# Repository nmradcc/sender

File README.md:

# sender
NMRA Conformance Test Software

This branch contains a refactor of the B 5.11.5 (V3-archive branch) reworked and retooled to support operation on modern PC (64bit Windows) with attached STM32 Nucleo controller for timing and IO.

The build tools are upgraded to build under Visual Studio Code with CMake.

The VSC C/C++ Extension Pack and CMake Tools extensions are required.

You can use the Visual Studio Build Tools 2022 Release - x86 as the build kit but others may work also.

There are two projects:
1. The host PC software
2. The STM32 controller (MCU) software

The send configuration files (*.INI) have been reworked to accept *.cfg files of the same format.

It will also accept legacy .INI files but is discuraged as using .INI files for parameter passing is a no-no in todays world.

Much of the documentation may still show .INI

Most of old Visual Source Safe (scc stuff) has been remove. See the V3-archive branch for previous history.

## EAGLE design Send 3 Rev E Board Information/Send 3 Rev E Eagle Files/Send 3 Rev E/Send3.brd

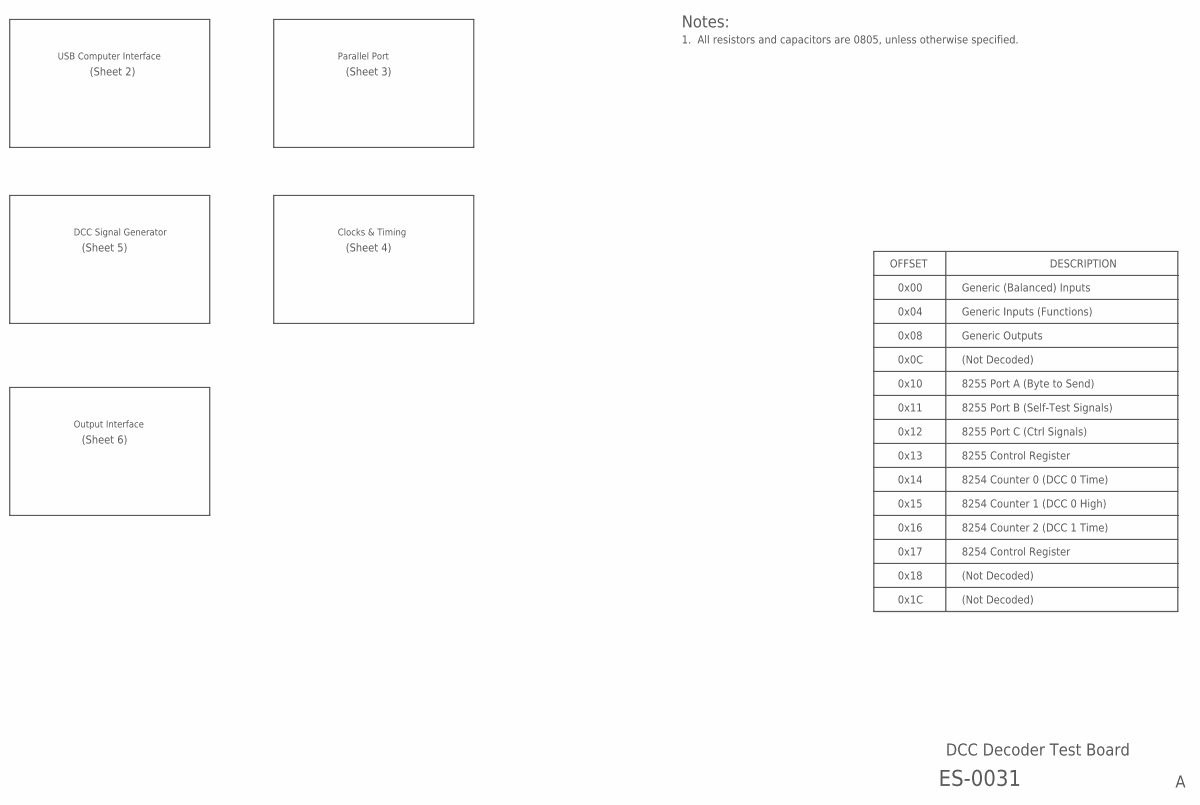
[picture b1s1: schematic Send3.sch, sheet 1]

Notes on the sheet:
USB Computer Interface
Notes:
1. All resistors and capacitors are 0805, unless otherwise specified.
Parallel Port
(Sheet 2)
(Sheet 3)
Clocks & Timing
(Sheet 4)
DCC Signal Generator
(Sheet 5)
Output Interface
(Sheet 6)
OFFSET
DESCRIPTION
0x00
0x04
0x08
0x10
0x11
0x12
0x13
0x14
0x15
0x16
0x17
Generic (Balanced) Inputs
Generic Inputs (Functions)
Generic Outputs
8255 Port A (Byte to Send)
8255 Port B (Self-Test Signals)
8255 Port C (Ctrl Signals)
8255 Control Register
8254 Counter 0 (DCC 0 Time)
8254 Counter 1 (DCC 0 High)
8254 Counter 2 (DCC 1 Time)
8254 Control Register
0x0C
0x18
0x1C
(Not Decoded)

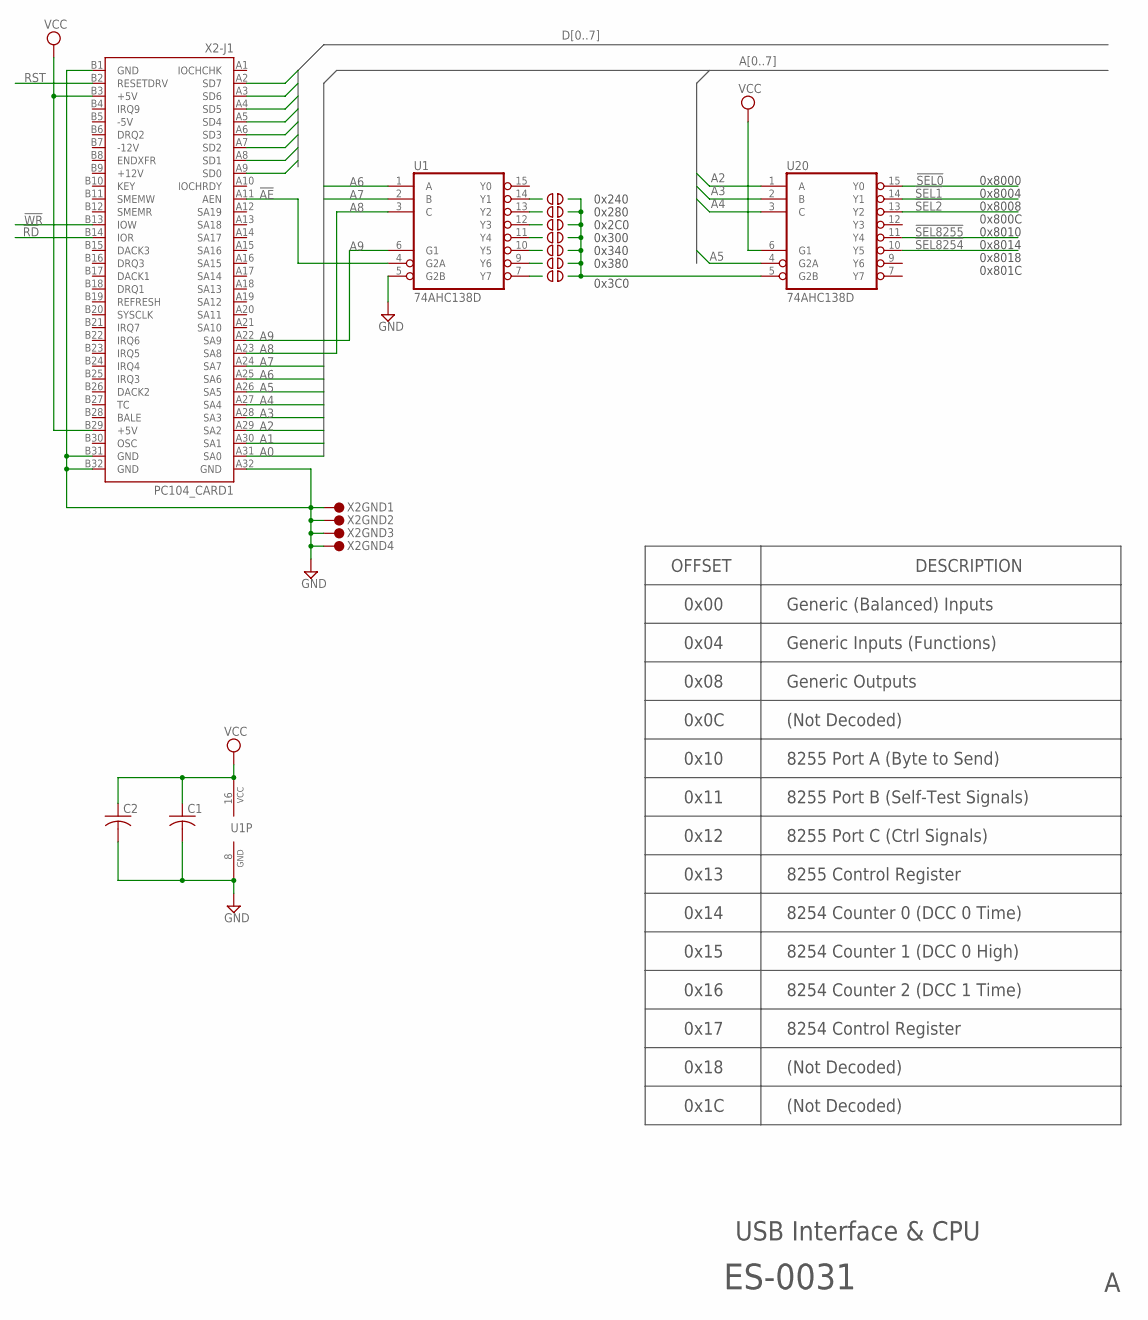
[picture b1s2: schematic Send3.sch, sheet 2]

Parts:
C1, C2: C-USC0805K; C0805K; MFG_PN ECJ-2VB1E104K
JMPR2, JMPR3, JMPR4, JMPR5, JMPR6, JMPR7, JMPR8: JUMPER; SOLDER_BRIDGE
U1, U20: 74AHC138D; SO16; MFG_PN SN74AHC138D
X2: PC104_CARD1; PC104-STANDARD

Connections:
!AE: U1.4 (G2A), X2.A11 (AEN)
!RD: X2.B14 (IOR); also elsewhere on the board
!SEL0: U20.15 (Y0); also elsewhere on the board
!SEL1: U20.14 (Y1); also elsewhere on the board
!SEL2: U20.13 (Y2); also elsewhere on the board
!SEL8254: U20.10 (Y5); also elsewhere on the board
!SEL8255: U20.11 (Y4); also elsewhere on the board
!WR: X2.B13 (IOW); also elsewhere on the board
A0: X2.A31 (SA0); also elsewhere on the board
A1: X2.A30 (SA1); also elsewhere on the board
A2: U20.1 (A), X2.A29 (SA2)
A3: U20.2 (B), X2.A28 (SA3)
A4: U20.3 (C), X2.A27 (SA4)
A5: U20.4 (G2A), X2.A26 (SA5)
A6: U1.1 (A), X2.A25 (SA6)
A7: U1.2 (B), X2.A24 (SA7)
A8: U1.3 (C), X2.A23 (SA8)
A9: U1.6 (G1), X2.A22 (SA9)
D0: X2.A9 (SD0); also elsewhere on the board
D1: X2.A8 (SD1); also elsewhere on the board
D2: X2.A7 (SD2); also elsewhere on the board
D3: X2.A6 (SD3); also elsewhere on the board
D4: X2.A5 (SD4); also elsewhere on the board
D5: X2.A4 (SD5); also elsewhere on the board
D6: X2.A3 (SD6); also elsewhere on the board
D7: X2.A2 (SD7); also elsewhere on the board
GND: C1.2, C2.2, U1.5 (G2B), U1.8 (GND), U20.8 (GND), X2.A32 (GND), X2.B1 (GND), X2.B31 (GND), X2.B32 (GND), X2.GND@1 (1), X2.GND@2 (1), X2.GND@3 (1), X2.GND@4 (1); also elsewhere on the board
unnamed: JMPR2.P$1, U1.14 (Y1)
unnamed: JMPR3.P$1, U1.13 (Y2)
unnamed: JMPR4.P$1, U1.12 (Y3)
unnamed: JMPR5.P$1, U1.11 (Y4)
unnamed: JMPR6.P$1, U1.10 (Y5)
unnamed: JMPR7.P$1, U1.9 (Y6)
unnamed: JMPR8.P$1, U1.7 (Y7)
unnamed: JMPR2.P$2, JMPR3.P$2, JMPR4.P$2, JMPR5.P$2, JMPR6.P$2, JMPR7.P$2, JMPR8.P$2, U20.5 (G2B)
RST: X2.B2 (RESETDRV); also elsewhere on the board
VCC: C1.1, C2.1, U1.16 (VCC), U20.6 (G1), U20.16 (VCC), X2.B3 (+5V), X2.B29 (+5V); also elsewhere on the board

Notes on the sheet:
USB Interface & CPU
OFFSET
DESCRIPTION
0x00
0x04
0x08
0x10
0x11
0x12
0x13
0x14
0x15
0x16
0x17
Generic (Balanced) Inputs
Generic Inputs (Functions)
Generic Outputs
8255 Port A (Byte to Send)
8255 Port B (Self-Test Signals)
8255 Port C (Ctrl Signals)
8255 Control Register
8254 Counter 0 (DCC 0 Time)
8254 Counter 1 (DCC 0 High)
8254 Counter 2 (DCC 1 Time)
8254 Control Register
0x0C
0x18
0x1C
(Not Decoded)
0x8000
0x8004
0x8008
0x800C
0x8010
0x8014
0x8018
0x801C
ES-0031
0x240
0x280

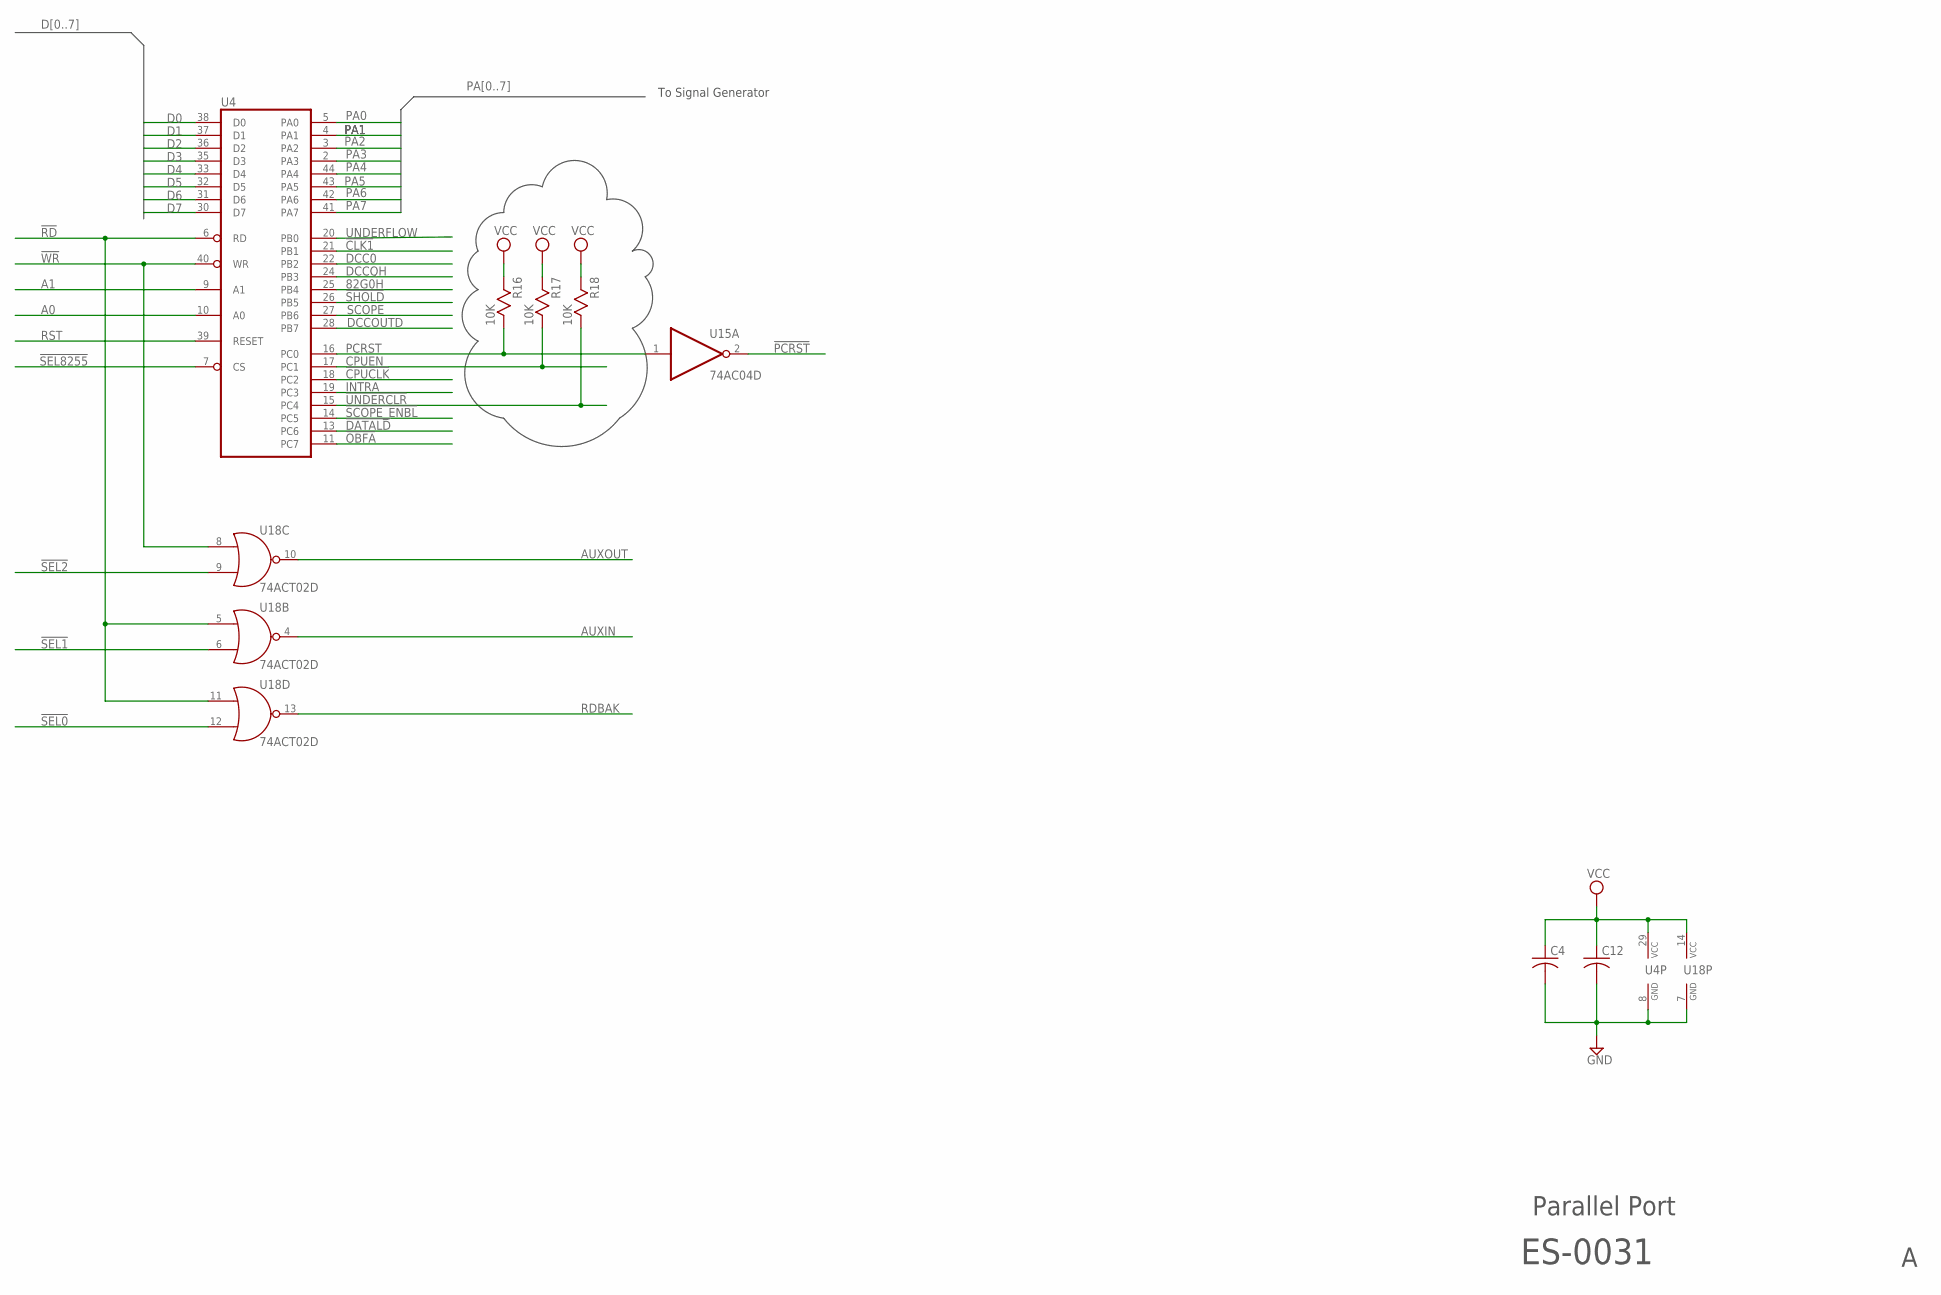
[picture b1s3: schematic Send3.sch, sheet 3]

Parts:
C4, C12: C-USC0805K; C0805K; MFG_PN ECJ-2VB1E104K
R16, R17, R18: 10K; R0805W; MFG_PN ERJ-P06J103V
U4: 8255A-S; PLCC44; MFG_PN CQ82C55AZ
U15: 74AC04D; SO14; MFG_PN SN74AHC04DR
U18: 74ACT02D; SO14; MFG_PN SN74AHC02DR

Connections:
82G0H: U4.25 (PB4); also elsewhere on the board
!CLK1: U4.21 (PB1); also elsewhere on the board
!CPUCLK: U4.18 (PC2); also elsewhere on the board
!DATALD: U4.13 (PC6); also elsewhere on the board
!OBFA: U4.11 (PC7); also elsewhere on the board
!PCRST: U15.2 (O); also elsewhere on the board
!RD: U4.6 (RD), U18.5 (I0), U18.11 (I0); also elsewhere on the board
!SCOPE_ENBL: U4.14 (PC5); also elsewhere on the board
!SEL0: U18.12 (I1); also elsewhere on the board
!SEL1: U18.6 (I1); also elsewhere on the board
!SEL2: U18.9 (I1); also elsewhere on the board
!SEL8255: U4.7 (CS); also elsewhere on the board
!SHOLD: U4.26 (PB5); also elsewhere on the board
!UNDERCLR: R18.2, U4.15 (PC4); also elsewhere on the board
!WR: U4.40 (WR), U18.8 (I0); also elsewhere on the board
A0: U4.10 (A0); also elsewhere on the board
A1: U4.9 (A1); also elsewhere on the board
AUXIN: U18.4 (O); also elsewhere on the board
AUXOUT: U18.10 (O); also elsewhere on the board
CPUEN: R17.2, U4.17 (PC1); also elsewhere on the board
D0: U4.38 (D0); also elsewhere on the board
D1: U4.37 (D1); also elsewhere on the board
D2: U4.36 (D2); also elsewhere on the board
D3: U4.35 (D3); also elsewhere on the board
D4: U4.33 (D4); also elsewhere on the board
D5: U4.32 (D5); also elsewhere on the board
D6: U4.31 (D6); also elsewhere on the board
D7: U4.30 (D7); also elsewhere on the board
DCC0: U4.22 (PB2); also elsewhere on the board
DCCOUTD: U4.28 (PB7); also elsewhere on the board
DCCQH: U4.24 (PB3); also elsewhere on the board
GND: C4.2, C12.2, U4.8 (GND), U18.7 (GND); also elsewhere on the board
INTRA: U4.19 (PC3)
PA0: U4.5 (PA0); also elsewhere on the board
PA1: U4.4 (PA1); also elsewhere on the board
PA2: U4.3 (PA2); also elsewhere on the board
PA3: U4.2 (PA3); also elsewhere on the board
PA4: U4.44 (PA4); also elsewhere on the board
PA5: U4.43 (PA5); also elsewhere on the board
PA6: U4.42 (PA6); also elsewhere on the board
PA7: U4.41 (PA7); also elsewhere on the board
PCRST: R16.2, U4.16 (PC0), U15.1 (I)
RDBAK: U18.13 (O); also elsewhere on the board
RST: U4.39 (RESET); also elsewhere on the board
SCOPE: U4.27 (PB6); also elsewhere on the board
UNDERFLOW: U4.20 (PB0); also elsewhere on the board
VCC: C4.1, C12.1, R16.1, R17.1, R18.1, U4.29 (VCC), U18.14 (VCC); also elsewhere on the board

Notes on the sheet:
Parallel Port
To Signal Generator
ES-0031

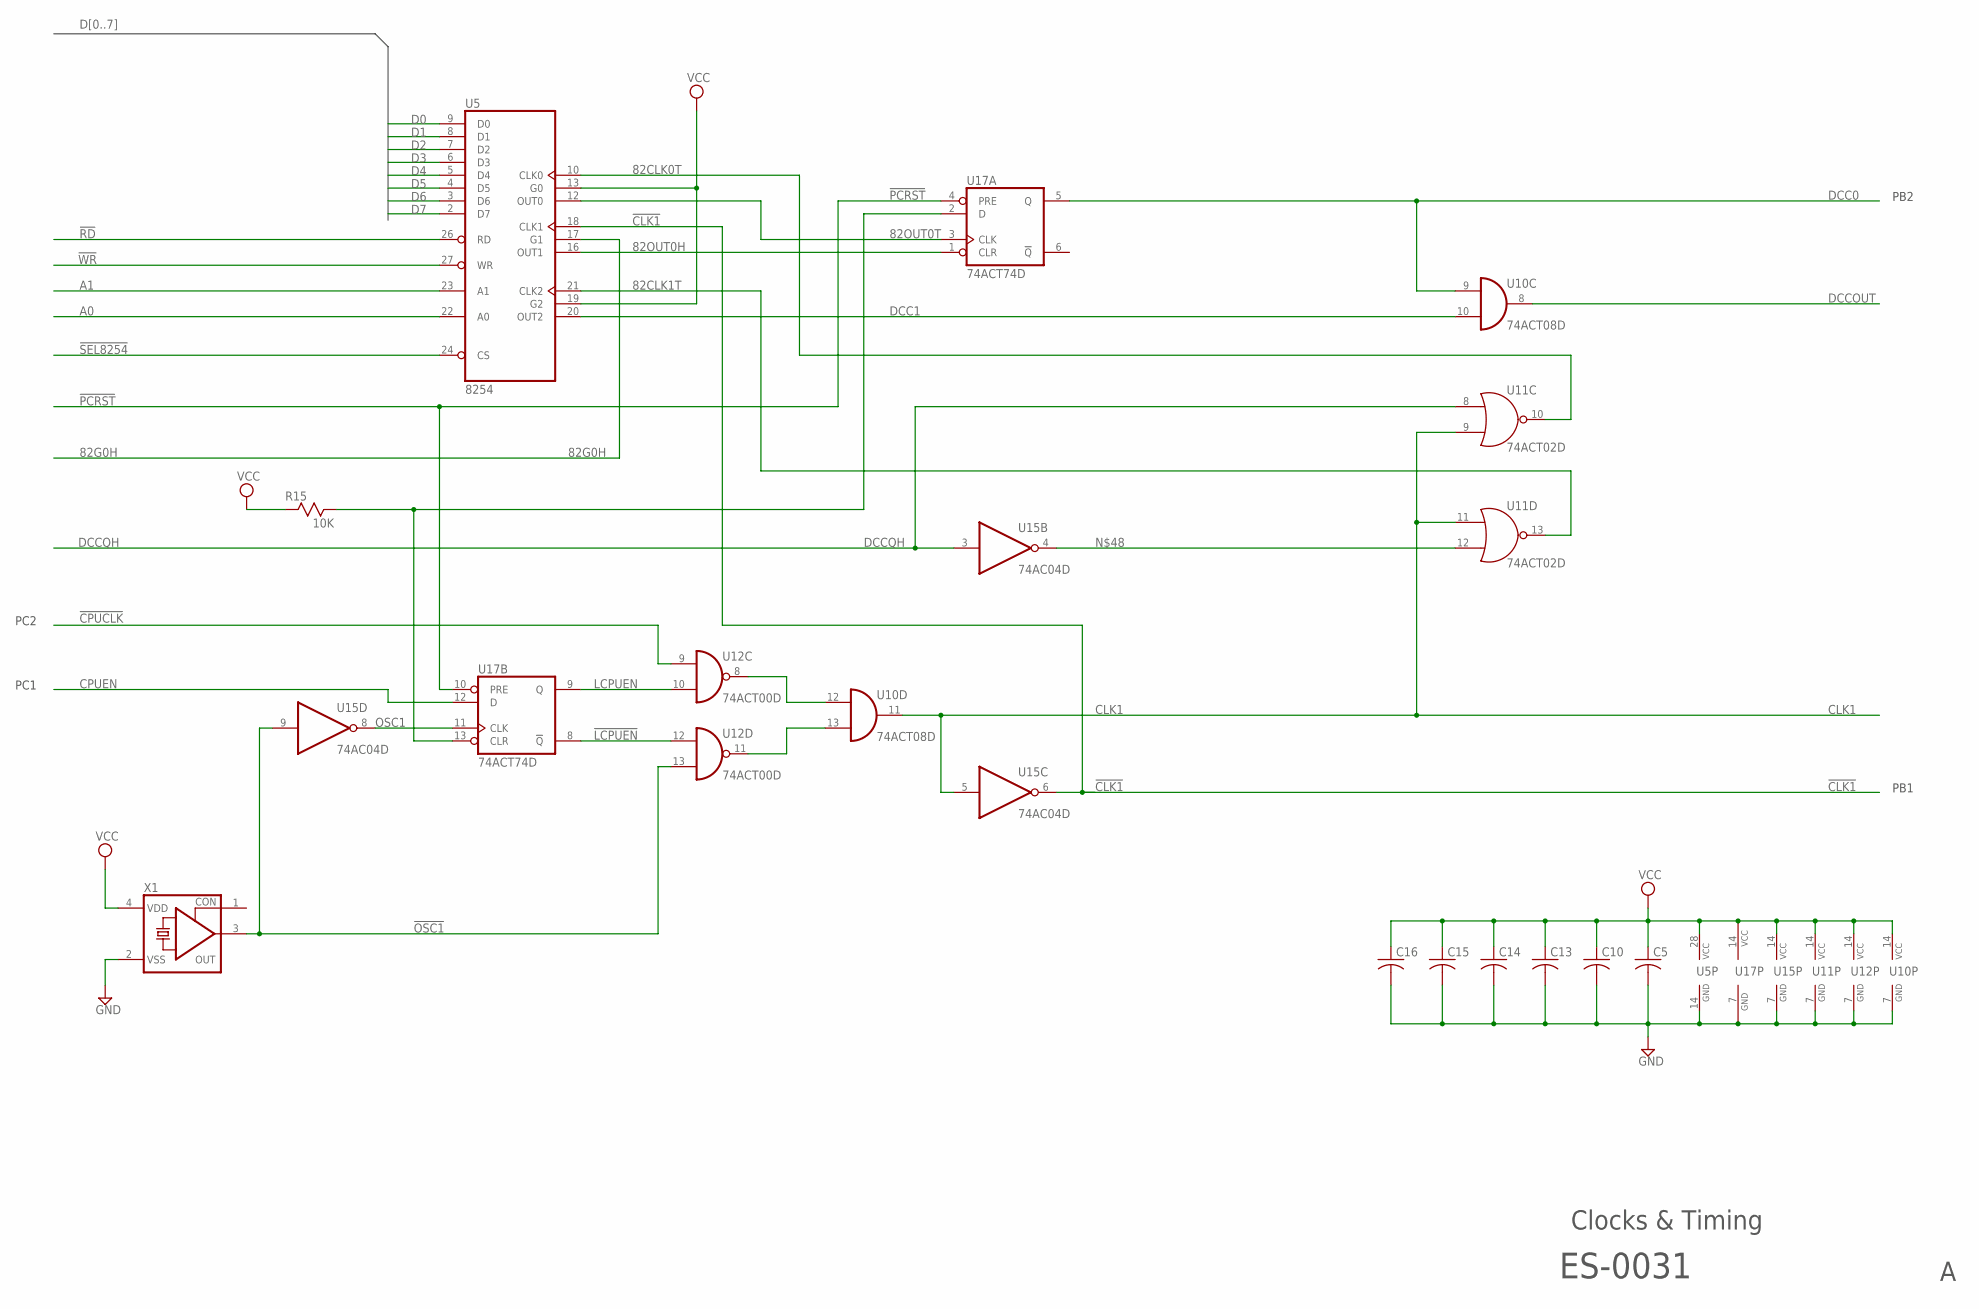
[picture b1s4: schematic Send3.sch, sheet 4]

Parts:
C5, C10, C13, C14, C15, C16: C-USC0805K; C0805K; MFG_PN ECJ-2VB1E104K
R15: 10K; R0805W; MFG_PN ERJ-P06J103V
U5: 8254; PLCC28S; MFG_PN CS82C54-10Z96
U10: 74ACT08D; SO14; MFG_PN SN74AHC08DR
U11: 74ACT02D; SO14; MFG_PN SN74AHC02DR
U12: 74ACT00D; SO14; MFG_PN SN74AHC00DR
U15: 74AC04D; SO14; MFG_PN SN74AHC04DR
U17: 74ACT74D; SO14; MFG_PN SN74AHC74DR
X1: CRYSTAL_RES-1100S; 1100S; MFG_PN ECS-8FM-1.00000

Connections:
82CLK0T: U5.10 (CLK0), U11.10 (O)
82CLK1T: U5.21 (CLK2), U11.13 (O)
82G0H: U5.17 (G1); also elsewhere on the board
82OUT0H: U5.16 (OUT1), U17.1 (CLR)
82OUT0T: U5.12 (OUT0), U17.3 (CLK)
!CLK1: U5.18 (CLK1), U15.6 (O); also elsewhere on the board
!CPUCLK: U12.9 (I0); also elsewhere on the board
!LCPUEN: U12.12 (I0), U17.8 (!Q)
!OSC1: U12.13 (I1), U15.9 (I), X1.3 (OUT)
!PCRST: U17.4 (PRE), U17.10 (PRE); also elsewhere on the board
!RD: U5.26 (RD); also elsewhere on the board
!SEL8254: U5.24 (CS); also elsewhere on the board
!WR: U5.27 (WR); also elsewhere on the board
A0: U5.22 (A0); also elsewhere on the board
A1: U5.23 (A1); also elsewhere on the board
CLK1: U10.11 (O), U11.9 (I1), U11.11 (I0), U15.5 (I); also elsewhere on the board
CPUEN: U17.12 (D); also elsewhere on the board
D0: U5.9 (D0); also elsewhere on the board
D1: U5.8 (D1); also elsewhere on the board
D2: U5.7 (D2); also elsewhere on the board
D3: U5.6 (D3); also elsewhere on the board
D4: U5.5 (D4); also elsewhere on the board
D5: U5.4 (D5); also elsewhere on the board
D6: U5.3 (D6); also elsewhere on the board
D7: U5.2 (D7); also elsewhere on the board
DCC0: U10.9 (I0), U17.5 (Q); also elsewhere on the board
DCC1: U5.20 (OUT2), U10.10 (I1)
DCCOUT: U10.8 (O); also elsewhere on the board
DCCQH: U11.8 (I0), U15.3 (I); also elsewhere on the board
GND: C5.2, C10.2, C13.2, C14.2, C15.2, C16.2, U5.14 (GND), U10.7 (GND), U11.7 (GND), U12.7 (GND), U15.7 (GND), U17.7 (GND), X1.2 (VSS); also elsewhere on the board
LCPUEN: U12.10 (I1), U17.9 (Q)
unnamed: U10.12 (I0), U12.8 (O)
unnamed: U10.13 (I1), U12.11 (O)
unnamed: U11.12 (I1), U15.4 (O)
OSC1: U15.8 (O), U17.11 (CLK)
PU403: R15.2, U17.2 (D), U17.13 (CLR)
VCC: C5.1, C10.1, C13.1, C14.1, C15.1, C16.1, R15.1, U5.13 (G0), U5.19 (G2), U5.28 (VCC), U10.14 (VCC), U11.14 (VCC), U12.14 (VCC), U15.14 (VCC), U17.14 (VCC), X1.4 (VDD); also elsewhere on the board

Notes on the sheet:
Clocks & Timing
PB2
PB1
PC1
PC2
ES-0031

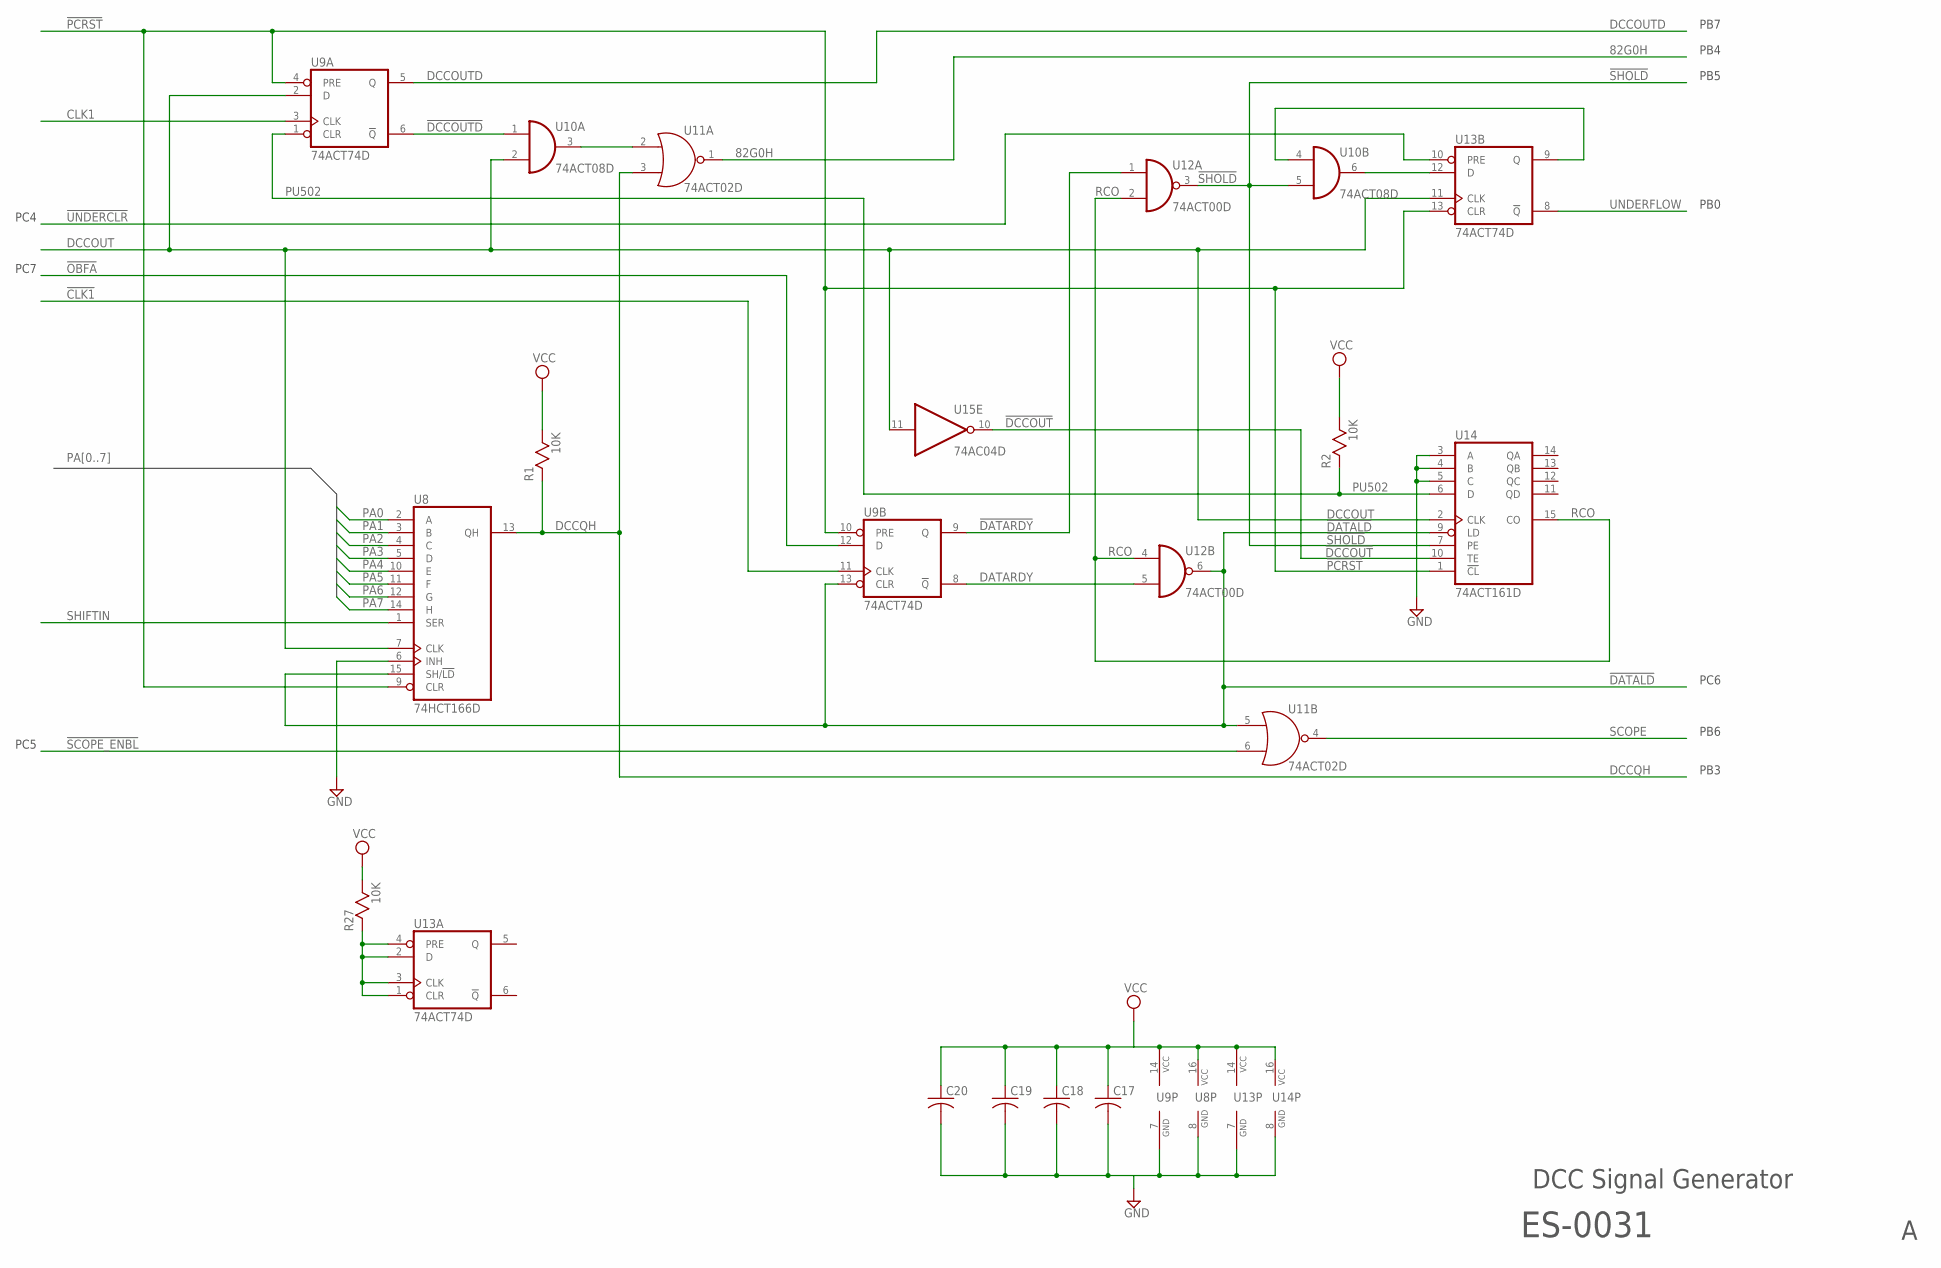
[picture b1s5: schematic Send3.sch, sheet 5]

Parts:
C17, C18, C19, C20: C-USC0805K; C0805K; MFG_PN ECJ-2VB1E104K
R1, R2, R27: 10K; R0805W; MFG_PN ERJ-P06J103V
U8: 74HCT166D; SO16; MFG_PN SN74HC166DR
U9, U13: 74ACT74D; SO14; MFG_PN SN74AHC74DR
U10: 74ACT08D; SO14; MFG_PN SN74AHC08DR
U11: 74ACT02D; SO14; MFG_PN SN74AHC02DR
U12: 74ACT00D; SO14; MFG_PN SN74AHC00DR
U14: 74ACT161D; SO16; MFG_PN CD74ACT161M
U15: 74AC04D; SO14; MFG_PN SN74AHC04DR

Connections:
82G0H: U11.1 (O); also elsewhere on the board
!CLK1: U9.11 (CLK); also elsewhere on the board
!DATALD: U8.15 (SH/!LD), U9.13 (CLR), U11.5 (I0), U12.6 (O), U14.9 (LD); also elsewhere on the board
!DATARDY: U9.9 (Q), U12.1 (I0)
!DCCOUT: U14.10 (TE), U15.10 (O)
!DCCOUTD: U9.6 (!Q), U10.1 (I0)
!OBFA: U9.12 (D); also elsewhere on the board
!PCRST: U8.9 (CLR), U9.4 (PRE), U9.10 (PRE), U13.13 (CLR), U14.1 (!CL); also elsewhere on the board
!SCOPE_ENBL: U11.6 (I1); also elsewhere on the board
!SHOLD: U10.5 (I1), U12.3 (O), U14.7 (PE); also elsewhere on the board
!UNDERCLR: U13.10 (PRE); also elsewhere on the board
CLK1: U9.3 (CLK); also elsewhere on the board
DATARDY: U9.8 (!Q), U12.5 (I1)
DCCOUT: U8.7 (CLK), U9.2 (D), U10.2 (I1), U13.11 (CLK), U14.2 (CLK), U15.11 (I); also elsewhere on the board
DCCOUTD: U9.5 (Q); also elsewhere on the board
DCCQH: R1.1, U8.13 (QH), U11.3 (I1); also elsewhere on the board
GND: C17.2, C18.2, C19.2, C20.2, U8.6 (INH), U8.8 (GND), U9.7 (GND), U13.7 (GND), U14.3 (A), U14.4 (B), U14.5 (C), U14.8 (GND); also elsewhere on the board
unnamed: U10.3 (O), U11.2 (I0)
unnamed: U10.6 (O), U13.12 (D)
unnamed: U10.4 (I0), U13.9 (Q)
unnamed: R27.1, U13.1 (CLR), U13.2 (D), U13.3 (CLK), U13.4 (PRE)
PA0: U8.2 (A); also elsewhere on the board
PA1: U8.3 (B); also elsewhere on the board
PA2: U8.4 (C); also elsewhere on the board
PA3: U8.5 (D); also elsewhere on the board
PA4: U8.10 (E); also elsewhere on the board
PA5: U8.11 (F); also elsewhere on the board
PA6: U8.12 (G); also elsewhere on the board
PA7: U8.14 (H); also elsewhere on the board
PU502: R2.1, U9.1 (CLR), U14.6 (D)
RCO: U12.2 (I1), U12.4 (I0), U14.15 (CO)
SCOPE: U11.4 (O); also elsewhere on the board
SHIFTIN: U8.1 (SER); also elsewhere on the board
UNDERFLOW: U13.8 (!Q); also elsewhere on the board
VCC: C17.1, C18.1, C19.1, C20.1, R1.2, R2.2, R27.2, U8.16 (VCC), U9.14 (VCC), U13.14 (VCC), U14.16 (VCC); also elsewhere on the board

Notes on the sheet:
DCC Signal Generator
PC4
PC7
PC5
PC6
PB0
PB7
PB4
PB5
PB6
PB3
ES-0031

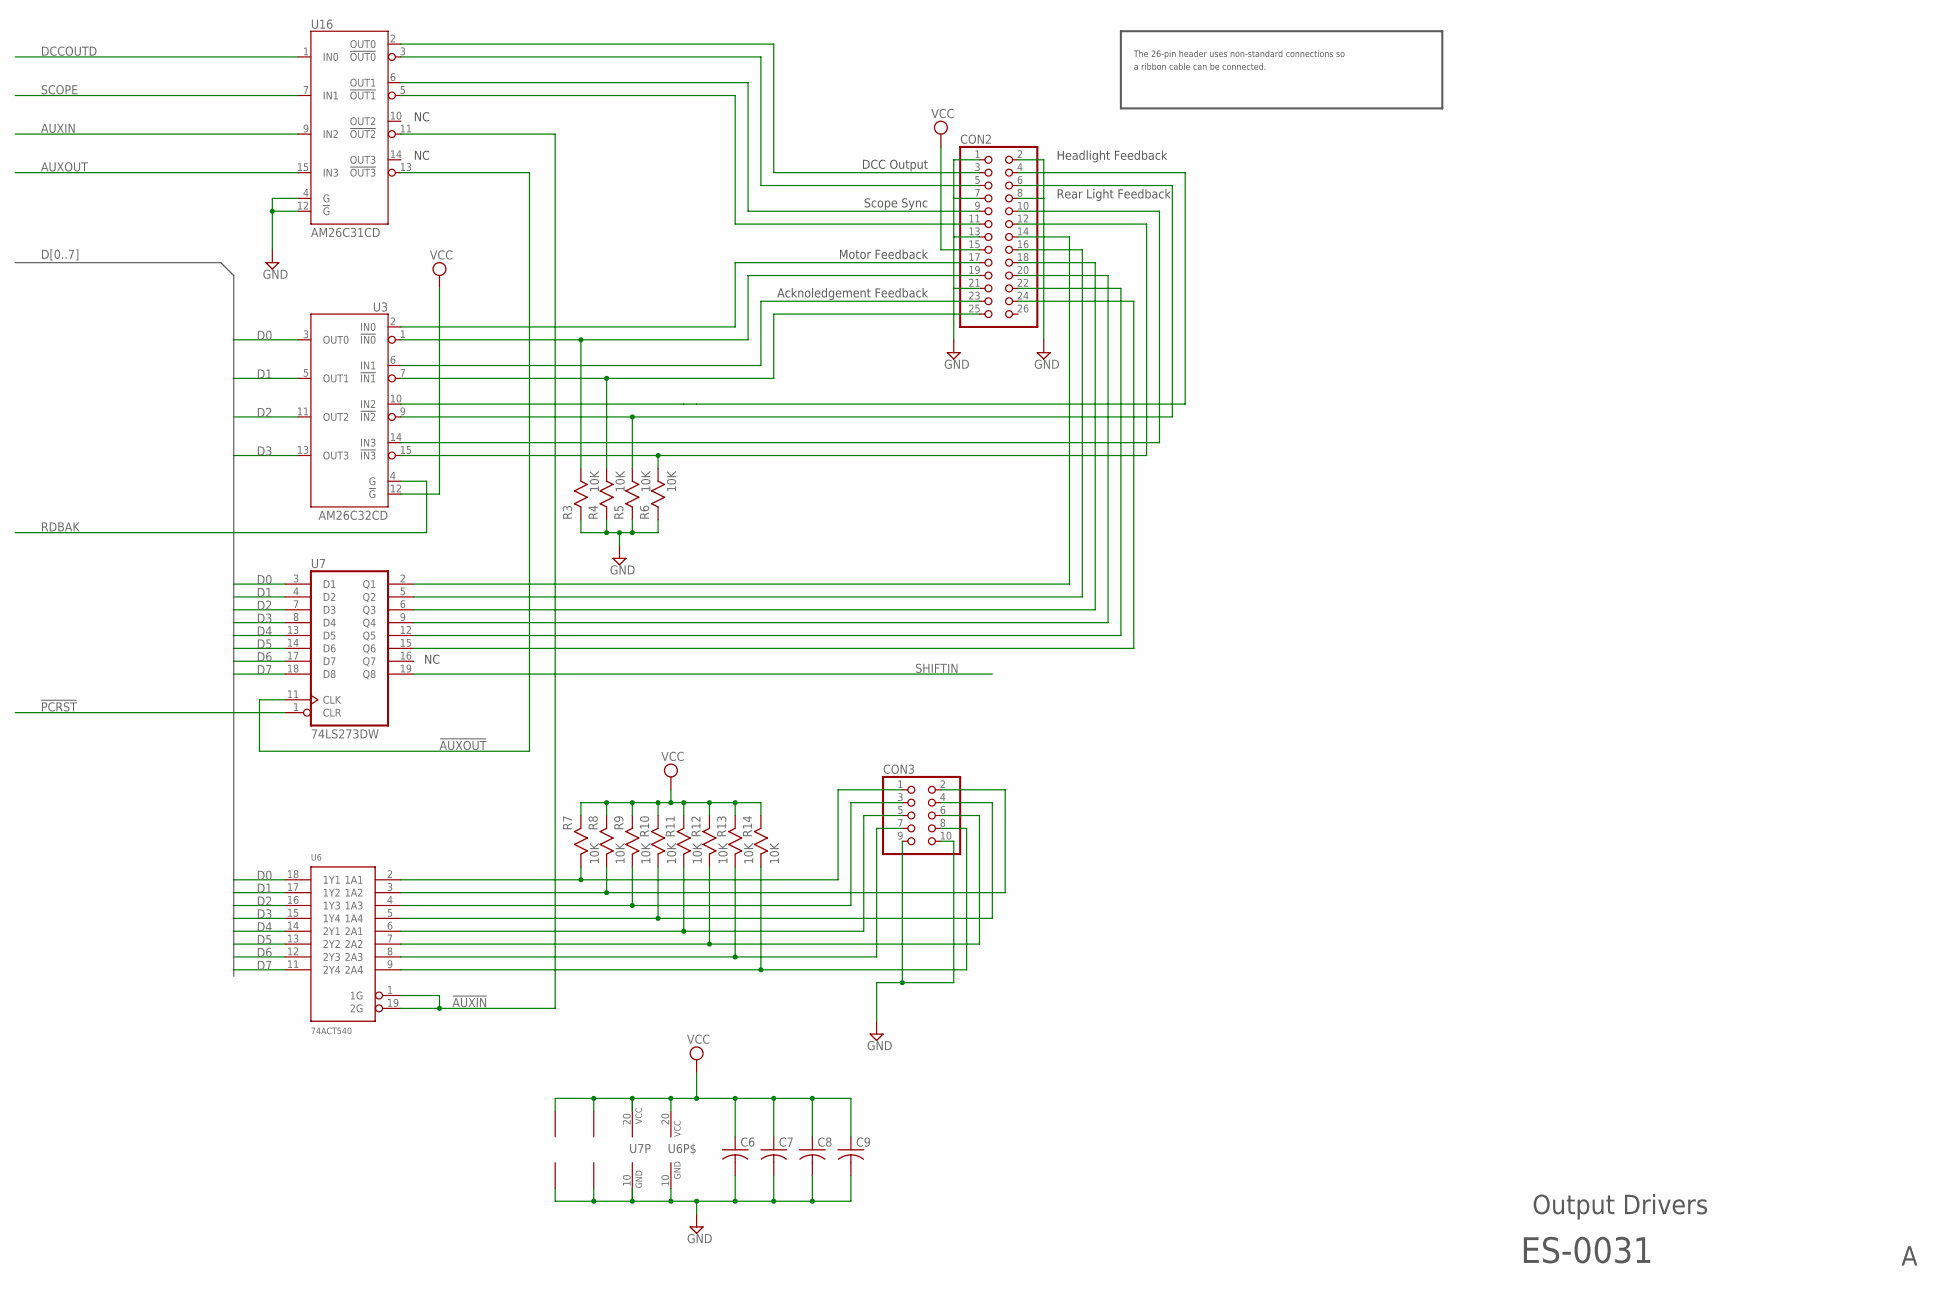
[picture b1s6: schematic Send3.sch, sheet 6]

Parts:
C6, C7, C8, C9: C-USC0805K; C0805K; MFG_PN ECJ-2VB1E104K
CON2: PINHD-2X13; 2X13; MFG_PN PBC36DFAN
CON3: PINHD-2X5; 2X05
R3, R4, R5, R6, R7, R8, R9, R10, R11, R12, R13, R14: 10K; R0805W; MFG_PN ERJ-P06J103V
U3: AM26C32CD; SO16; MFG_PN AM26C32CD
U6: 74ACT540; SO20W; MFG_PN SN74AHC540DWR
U7: 74LS273DW; SO20W; MFG_PN SN74LS273DW
U16: AM26C31CD; SO16; MFG_PN AM26C31QDRG4

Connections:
!ACK_FEEDBACK: CON2.25, R4.2, U3.7 (!IN1)
!AUXIN: U6.1 (1G), U6.19 (2G), U16.11 (!OUT2)
!AUXOUT: U7.11 (CLK), U16.13 (!OUT3)
!DCC_OUT: CON2.5, U16.3 (!OUT0)
!HL_FEEDBACK: CON2.6, R5.2, U3.9 (!IN2)
!MOTOR_FEEDBACK: CON2.19, R3.2, U3.1 (!IN0)
!PCRST: U7.1 (CLR); also elsewhere on the board
!RL_FEEDBACK: CON2.12, R6.2, U3.15 (!IN3)
!SCOPE_SYNC: CON2.11, U16.5 (!OUT1)
ACK_FEEDBACK: CON2.23, U3.6 (IN1)
AUXIN: U16.9 (IN2); also elsewhere on the board
AUXOUT: U16.15 (IN3); also elsewhere on the board
D0: U3.3 (OUT0), U6.18 (1Y1), U7.3 (D1); also elsewhere on the board
D1: U3.5 (OUT1), U6.17 (1Y2), U7.4 (D2); also elsewhere on the board
D2: U3.11 (OUT2), U6.16 (1Y3), U7.7 (D3); also elsewhere on the board
D3: U3.13 (OUT3), U6.15 (1Y4), U7.8 (D4); also elsewhere on the board
D4: U6.14 (2Y1), U7.13 (D5); also elsewhere on the board
D5: U6.13 (2Y2), U7.14 (D6); also elsewhere on the board
D6: U6.12 (2Y3), U7.17 (D7); also elsewhere on the board
D7: U6.11 (2Y4), U7.18 (D8); also elsewhere on the board
DCCOUTD: U16.1 (IN0); also elsewhere on the board
DCC_OUT: CON2.3, U16.2 (OUT0)
F1: CON3.1, R7.2, U6.2 (1A1)
F2: CON3.2, R8.2, U6.3 (1A2)
F3: CON3.3, R9.2, U6.4 (1A3)
F4: CON3.4, R10.2, U6.5 (1A4)
F5: CON3.5, R11.2, U6.6 (2A1)
F6: CON3.6, R12.2, U6.7 (2A2)
F7: CON3.7, R13.2, U6.8 (2A3)
F8: CON3.8, R14.2, U6.9 (2A4)
GND: C6.2, C7.2, C8.2, C9.2, CON2.1, CON2.2, CON2.7, CON2.8, CON2.13, CON2.21, CON3.9, CON3.10, R3.1, R4.1, R5.1, R6.1, U3.8 (GND), U6.10 (GND), U7.10 (GND), U16.4 (G), U16.8 (GND), U16.12 (!G); also elsewhere on the board
HL_FEEDBACK: CON2.4, U3.10 (IN2)
MOTOR_FEEDBACK: CON2.17, U3.2 (IN0)
unnamed: CON2.14, U7.2 (Q1)
unnamed: CON2.16, U7.5 (Q2)
unnamed: CON2.18, U7.6 (Q3)
unnamed: CON2.20, U7.9 (Q4)
unnamed: CON2.22, U7.12 (Q5)
unnamed: CON2.24, U7.15 (Q6)
RDBAK: U3.4 (G); also elsewhere on the board
RL_FEEDBACK: CON2.10, U3.14 (IN3)
SCOPE: U16.7 (IN1); also elsewhere on the board
SCOPE_SYNC: CON2.9, U16.6 (OUT1)
SHIFTIN: U7.19 (Q8); also elsewhere on the board
VCC: C6.1, C7.1, C8.1, C9.1, CON2.15, R7.1, R8.1, R9.1, R10.1, R11.1, R12.1, R13.1, R14.1, U3.12 (!G), U3.16 (VCC), U6.20 (VCC), U7.20 (VCC), U16.16 (VCC); also elsewhere on the board

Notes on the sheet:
Output Drivers
ES-0031
Motor Feedback
Scope Sync
DCC Output
Acknoledgement Feedback
Headlight Feedback
Rear Light Feedback
The 26-pin header uses non-standard connections so
a ribbon cable can be connected.

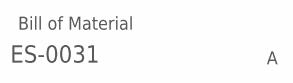
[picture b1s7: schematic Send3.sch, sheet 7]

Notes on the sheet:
Bill of Material
ES-0031

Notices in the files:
Send 3 Rev E Board Information/Send 3 Rev E Eagle Files/Send 3 Rev E/Send3.brd:
(C) 2010, BY BRIAN BARNT
